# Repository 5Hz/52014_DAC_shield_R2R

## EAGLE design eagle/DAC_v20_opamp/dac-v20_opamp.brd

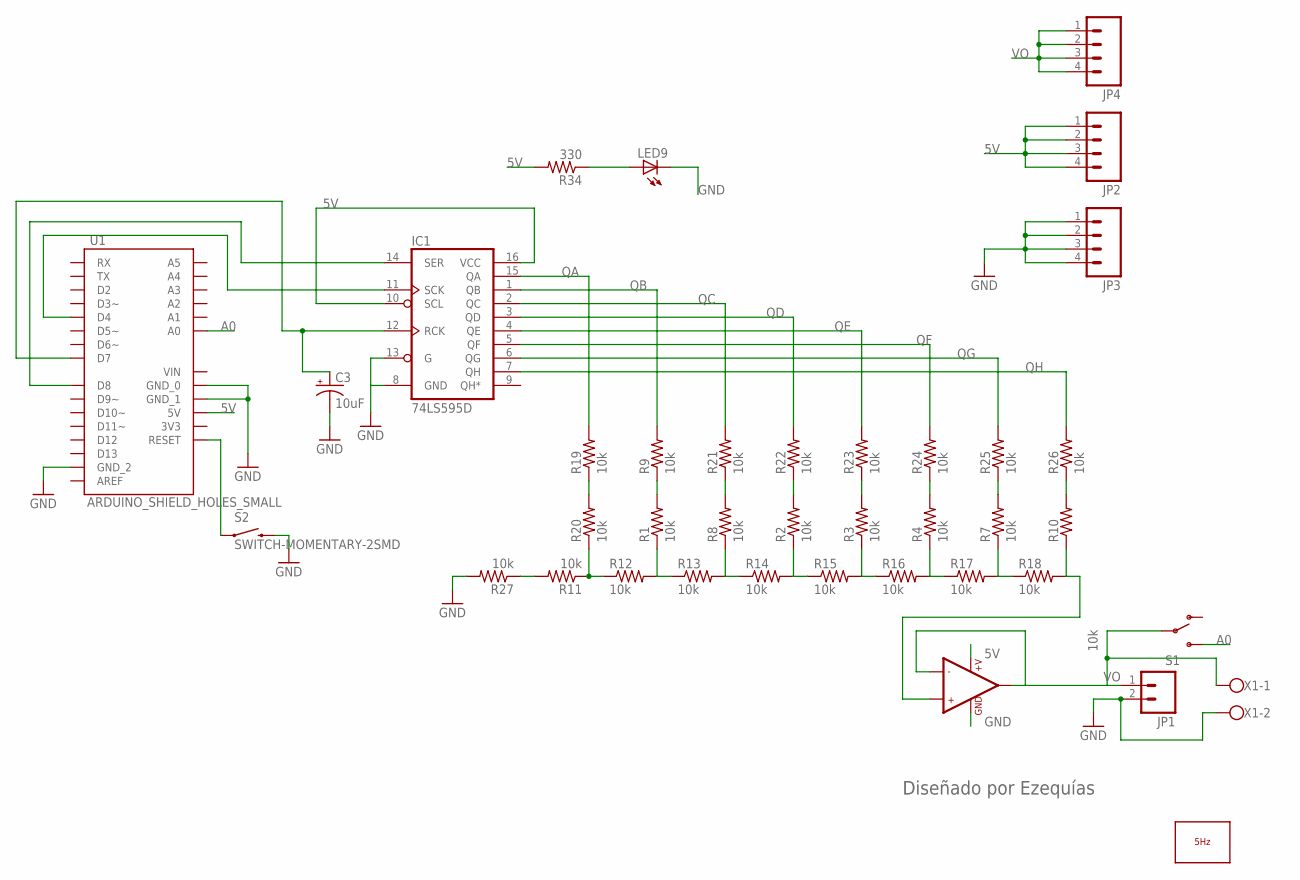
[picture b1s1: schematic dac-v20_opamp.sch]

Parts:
C3: 10uF; EIA3216
IC1: 74LS595D; SO16
JP1: M02POLAR; MOLEX-1X2
JP2, JP3, JP4: M04PTH; 1X04
LED9: LED0603; LED-0603
LOGO2: LOGO_5HZ_H_20MM; 5HZ_LOGO_H_20MM
R1, R2, R3, R4, R7, R8, R9, R10, R11, R12, R13, R14, R15, R16, R17, R18, R19, R20, R21, R22, R23, R24, R25, R26, R27: 10k; 0603-RES
R34: 330; 0603-RES
S1: SWITCH-SPSTPTH; SWITCH-SPDT
S2: SWITCH-MOMENTARY-2SMD; TACTILE_SWITCH_SMD
U1: ARDUINO_SHIELD_HOLES_SMALL; UNO_SHIELD_SMALL_HOLES
U$1: LMV358; SO08
X1: W237-102M2; W237-102

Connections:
5V: IC1.10 (SCL), IC1.16 (VCC), JP2.1, JP2.2, JP2.3, JP2.4, R34.2, U1.5V, U$1.8 (+V)
A0: S1.3 (S), U1.A0
GND: C3.C (-), IC1.8 (GND), IC1.13 (G), JP1.2, JP3.1, JP3.2, JP3.3, JP3.4, LED9.C, R27.2, S2.3 (2), U1.GND_0, U1.GND_1, U1.GND_2, U$1.4 (GND), X1.2
unnamed: IC1.14 (SER), U1.D8
unnamed: S2.1, U1.RES (RESET)
unnamed: IC1.11 (SCK), U1.D4
unnamed: C3.A (+), IC1.12 (RCK), U1.D7
unnamed: LED9.A, R34.1
unnamed: R10.1, R18.2, U$1.3 (+IN1)
unnamed: R11.1, R12.1, R20.1
unnamed: R1.1, R12.2, R13.1
unnamed: R8.1, R13.2, R14.1
unnamed: R2.1, R14.2, R15.1
unnamed: R3.1, R15.2, R16.1
unnamed: R19.1, R20.2
unnamed: R1.2, R9.1
unnamed: R4.1, R16.2, R17.1
unnamed: R8.2, R21.1
unnamed: R7.1, R17.2, R18.1
unnamed: R10.2, R26.1
unnamed: R7.2, R25.1
unnamed: R4.2, R24.1
unnamed: R3.2, R23.1
unnamed: R2.2, R22.1
unnamed: R11.2, R27.1
QA: IC1.15 (QA), R19.2
QB: IC1.1 (QB), R9.2
QC: IC1.2 (QC), R21.2
QD: IC1.3 (QD), R22.2
QE: IC1.4 (QE), R23.2
QF: IC1.5 (QF), R24.2
QG: IC1.6 (QG), R25.2
QH: IC1.7 (QH), R26.2
VO: JP1.1, JP4.1, JP4.2, JP4.3, JP4.4, S1.2, U$1.1 (OUT1), U$1.2 (-IN1), X1.1

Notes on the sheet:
Diseñado por Ezequías

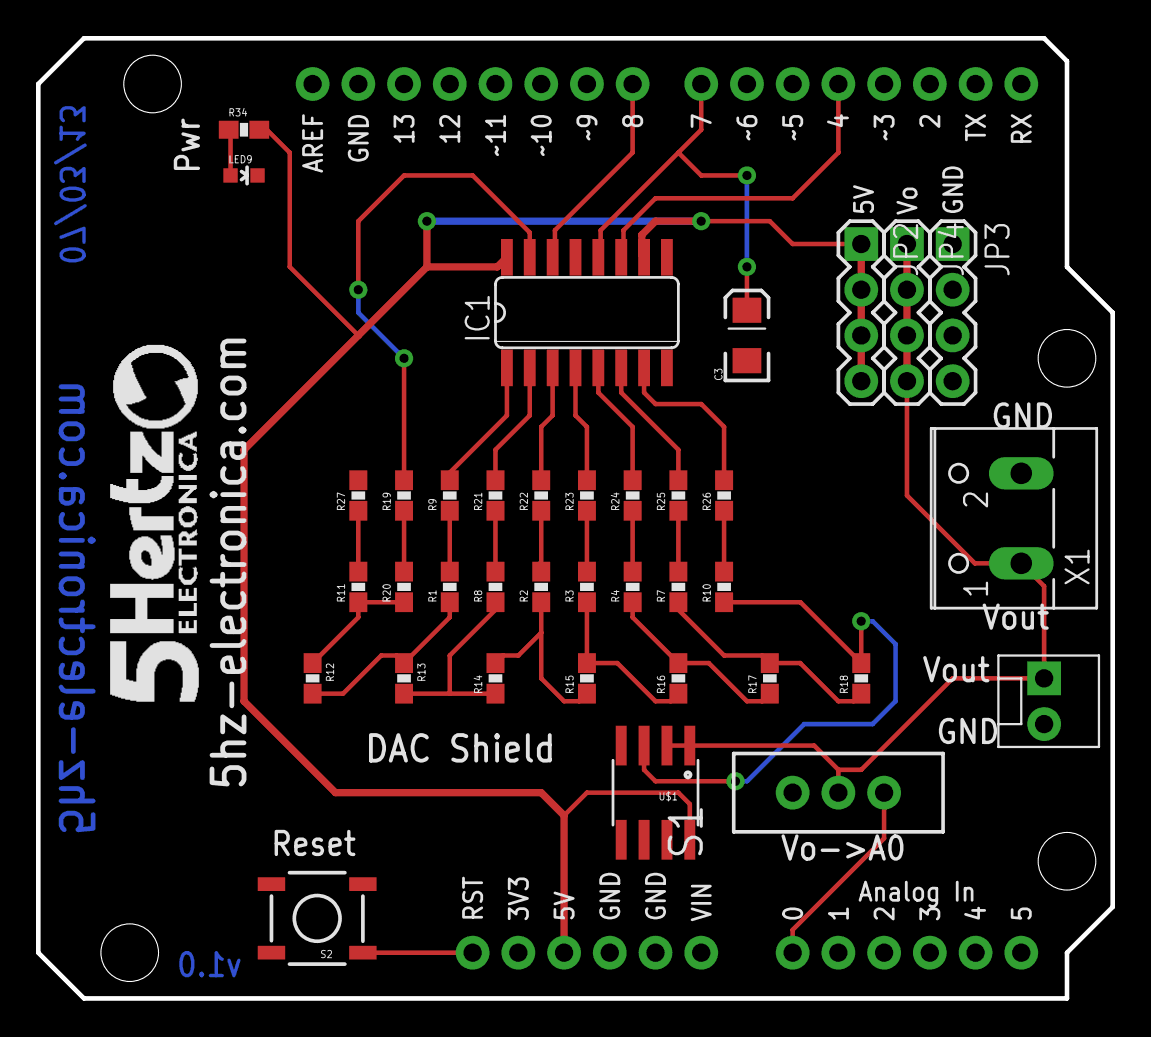
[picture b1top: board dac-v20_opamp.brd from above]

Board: 2 copper layers, 59.7 x 53.3 mm, 39 parts (0 on the bottom side), 34 nets.

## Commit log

2014-01-14 creación

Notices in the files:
parts and their libraries:
memory-atmel-2: Licensing: CC v3.0 Share-Alike You are welcome to use this library for commercial purposes.
